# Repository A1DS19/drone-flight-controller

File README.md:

# Drone Flight Controller

A custom drone flight controller, designed in KiCad 10: an STM32F103R8T6 flight core paired with
an ATmega328P telemetry co-processor on a four-layer, ~102 × 49 mm PCB — taken from schematic
capture through placement, routing, clean ERC/DRC, and JLCPCB fabrication outputs
([pcb/production/](pcb/production/)).

## Features

- **STM32F103R8T6 flight core** — MPU-6050 IMU on I²C, four ESC/motor outputs, RC-receiver and
  TF-Luna LIDAR inputs, USB with ESD protection, SWD debug
- **ATmega328P telemetry co-processor** — nRF24L01P 2.4 GHz radio with SMA antenna connector,
  CH340G USB-serial, microSD logging over SPI, 5 V ↔ 3.3 V level shifting
- **Power tree** — XT60 battery input → LM7805 (5 V) → AMS1117 (3.3 V), filtered analog rail,
  battery-voltage sensing
- **0.96″ OLED** status display
- **Four-layer board** — solid internal ground plane, dedicated power planes, 71-line LCSC BOM,
  JLCPCB-ready Gerbers

## Screenshots

| Front | Back |
|-------|------|
|  |  |

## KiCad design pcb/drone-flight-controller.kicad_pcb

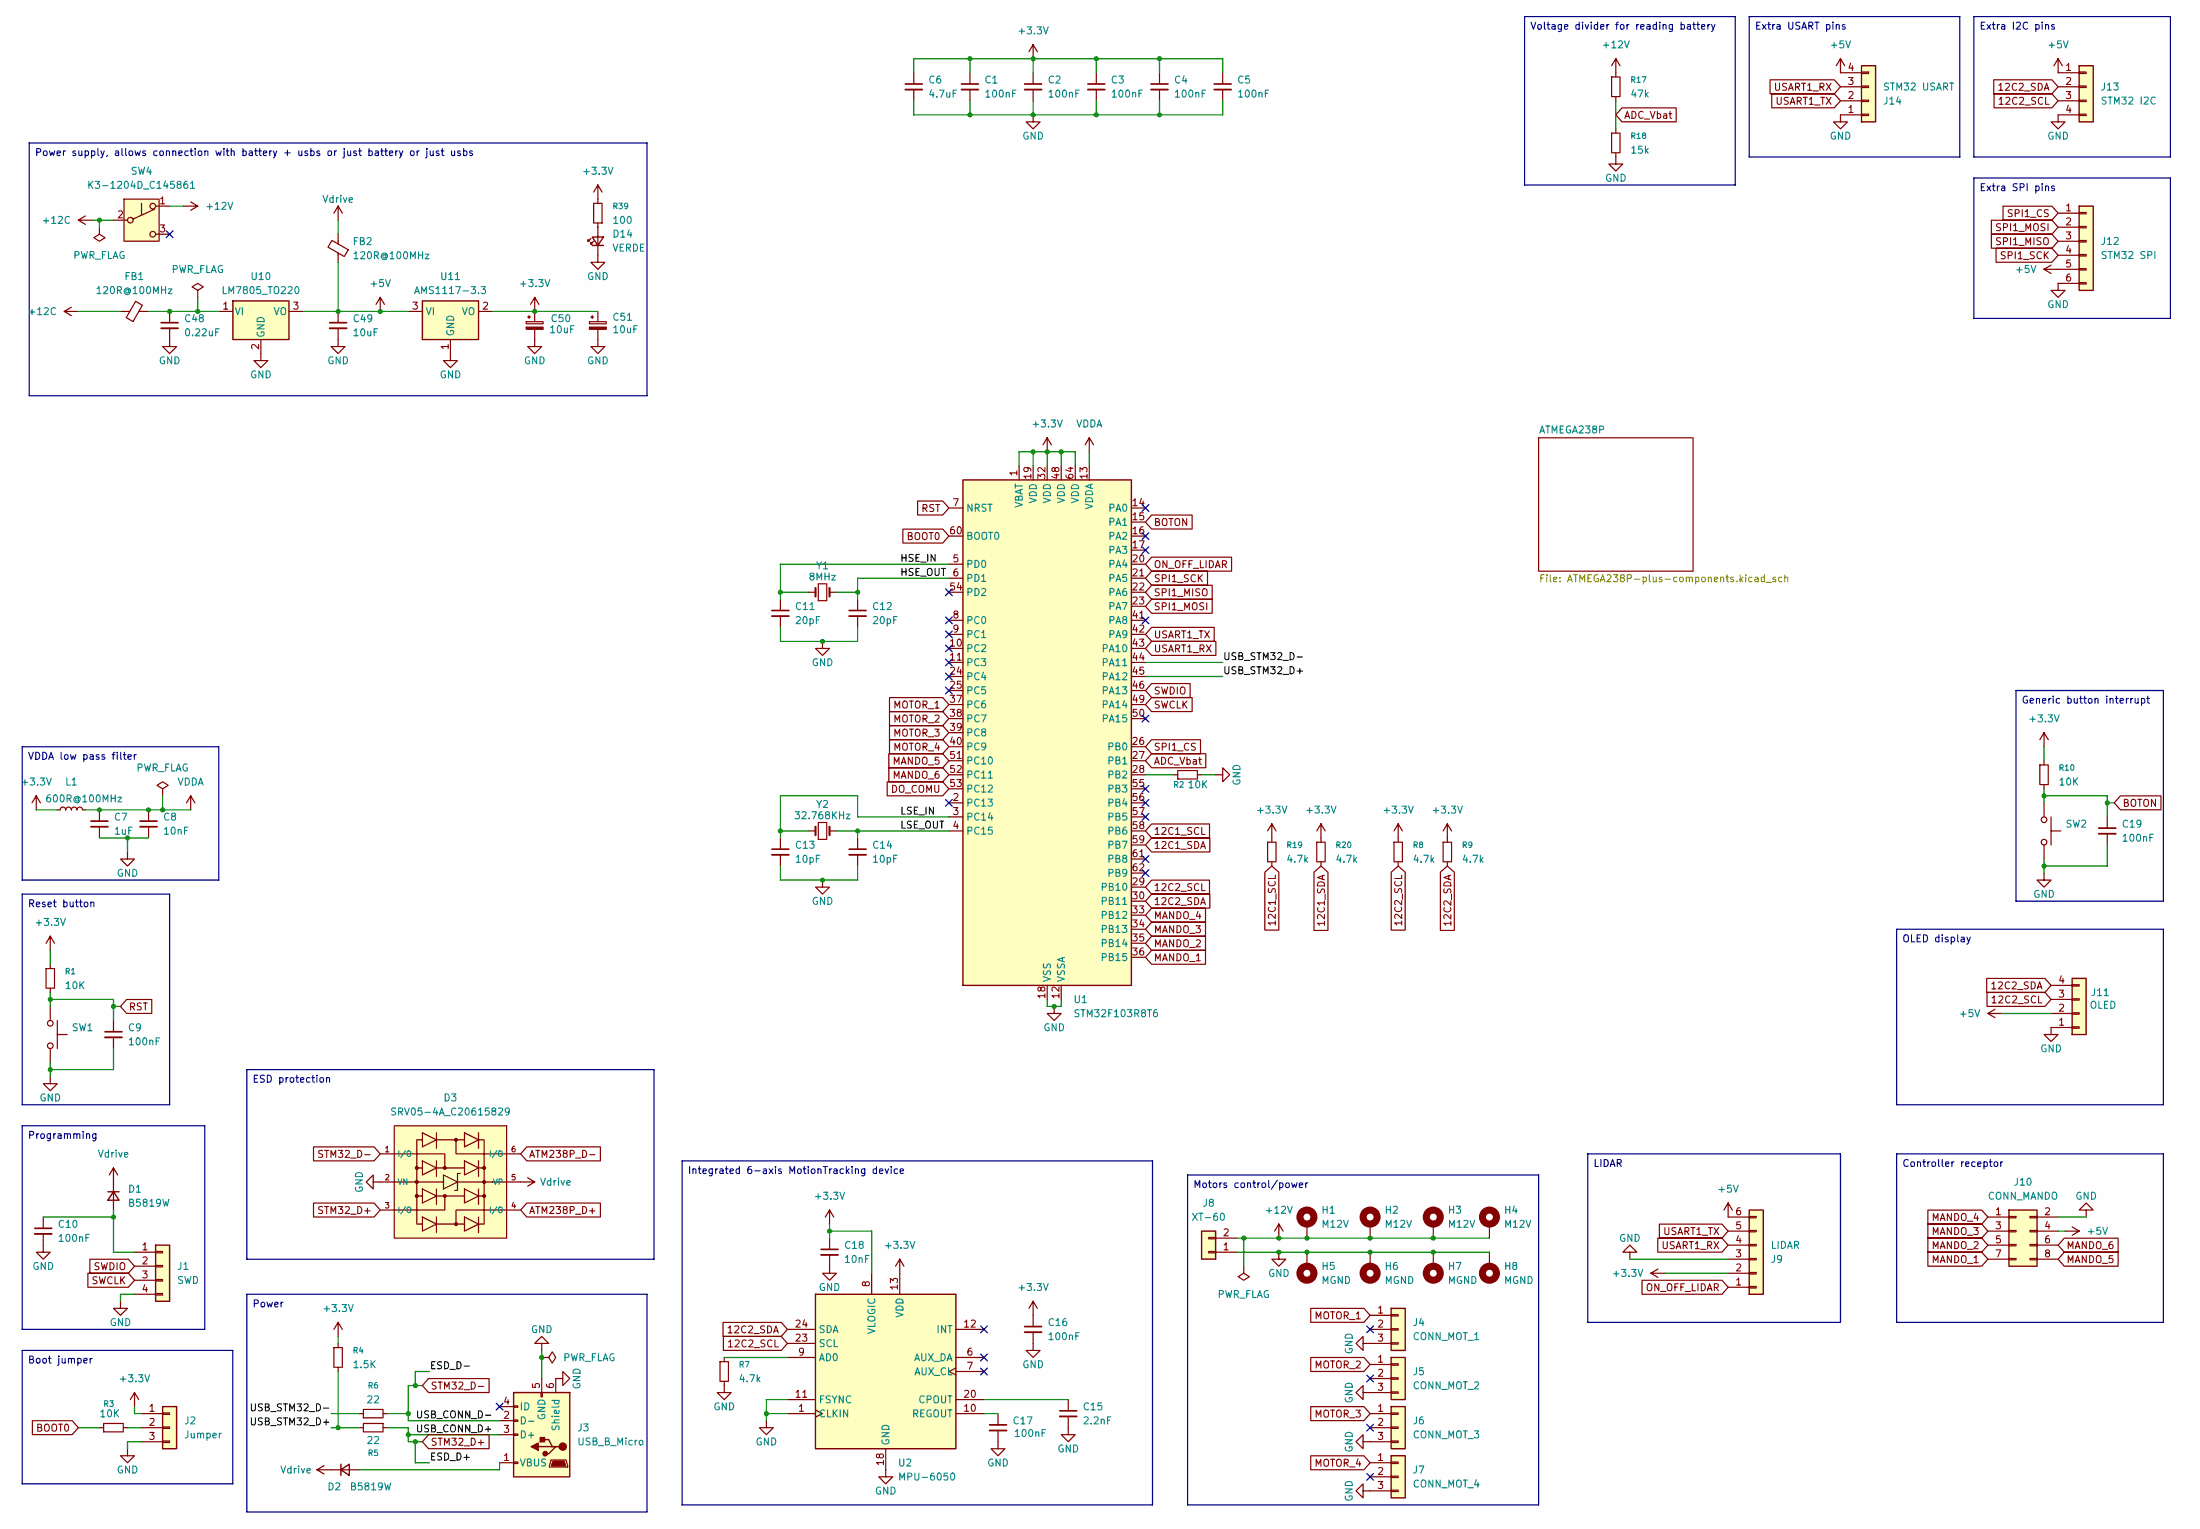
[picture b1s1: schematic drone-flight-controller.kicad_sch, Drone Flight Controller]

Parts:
C1, C2, C3, C4, C5, C9, C10, C16, C17, C19: 100nF; C_0402_1005Metric; Part CL05B104KO5NNNC; LCSC C1525
C6: 4.7uF; C_0402_1005Metric; Part CL05A475MQ5NRNC; LCSC C307423
C7: 1uF; C_0402_1005Metric; Part CL05A105KA5NQNC; LCSC C52923
C8, C18: 10nF; C_0402_1005Metric; Part CL05B103KB5NNNC; LCSC C15195
C11, C12: 20pF; C_0402_1005Metric; Part 0402CG200J500NT; LCSC C1554
C13, C14: 10pF; C_0402_1005Metric; Part CL05C100JB5NNNC; LCSC C32949
C15: 2.2nF; C_0402_1005Metric; Part 0402B222K500NT; LCSC C1531
C48: 0.22uF; C_1206_3216Metric; Part 1206B224K500NT; LCSC C1857
C49: 10uF; C_1206_3216Metric; Part CL31A106KBHNNNE; LCSC C13585
C50, C51: 10uF; C_1206_3216Metric; Part TAJA106K016RNJ; LCSC C7171
D1, D2: B5819W; D_SOD-123; Part B5819W; LCSC C64885
D3: SRV05-4A_C20615829; SOT-23-6_L2.9-W1.6-P0.95-LS2.9-BL; Part SRV05-4A; LCSC C20615829
D14: VERDE; LED_0603_1608Metric; Part KT-0603G; LCSC C12624
FB1, FB2: 120R@100MHz; L_0805_2012Metric; Part BLM21PG121SN1D; LCSC C79382
H1, H2, H3, H4: M12V; MountingHole_3.5mm_5.5mm
H5, H6, H7, H8: MGND; MountingHole_3.5mm_5.5mm
J1: SWD; PinHeader_1x04_P2.54mm_Vertical; Part PZ254V-11-04P; LCSC C2691448
J2: Jumper; PinHeader_1x03_P2.54mm_Vertical; Part PZ254V-11-03P; LCSC C2937625
J3: USB_B_Micro; MICRO-USB-SMD_MICROXNJ_1; Part MicroXNJ; LCSC C404969
J4: CONN_MOT_1; PinHeader_1x03_P2.54mm_Vertical; Part PZ254V-11-03P; LCSC C2937625
J5: CONN_MOT_2; PinHeader_1x03_P2.54mm_Vertical; Part PZ254V-11-03P; LCSC C2937625
J6: CONN_MOT_3; PinHeader_1x03_P2.54mm_Vertical; Part PZ254V-11-03P; LCSC C2937625
J7: CONN_MOT_4; PinHeader_1x03_P2.54mm_Vertical; Part PZ254V-11-03P; LCSC C2937625
J8: XT-60; AMASS_XT60-M; Part XT60-M.; LCSC C98733
J9: LIDAR; PinHeader_1x06_P2.54mm_Horizontal; Part PZ254V-11-06P; LCSC C492405
J10: CONN_MANDO; PinHeader_2x04_P2.54mm_Vertical; Part PZ254V-12-8P; LCSC C492421
J11: OLED; Part PZ254V-11-04P; LCSC C2691448
J12: STM32 SPI; PinHeader_1x06_P2.54mm_Vertical; Part PZ254V-11-06P; LCSC C492405
J13: STM32 I2C; PinHeader_1x04_P2.54mm_Vertical; Part PZ254V-11-04P; LCSC C2691448
J14: STM32 USART; PinHeader_1x04_P2.54mm_Horizontal; Part PZ254V-11-04P; LCSC C2691448
L1: 600R@100MHz; L_0402_1005Metric; Part BLM15AG601SN1D; LCSC C76884
R1, R2, R3, R10: 10K; R_0402_1005Metric; Part 0402WGF1002TCE; LCSC C25744
R4: 1.5K; R_0402_1005Metric; Part 0402WGF1501TCE; LCSC C25867
R5, R6: 22; R_0603_1608Metric; Part 0402WGF220JTCE; LCSC C25092
R7, R8, R9, R19, R20: 4.7k; R_0402_1005Metric; Part 0402WGF4701TCE; LCSC C25900
R17: 47k; R_0402_1005Metric; Part 0402WGF4702TCE; LCSC C25792
R18: 15k; R_0402_1005Metric; Part 0402WGF1502TCE; LCSC C25756
R39: 100; R_0603_1608Metric; Part 0402WGF1000TCE; LCSC C25076
SW1, SW2: TS-1088-AR02016_C720477; SW-SMD_L3.9-W3.0-P4.45; Part TS-1088-AR02016; LCSC C720477
SW4: K3-1204D_C145861; SW-TH_K3-1204D; Part K3-1204D; LCSC C145861
U1: STM32F103R8T6; LQFP-64_10x10mm_P0.5mm; Part STM32F103R8T6; LCSC C46034
U2: MPU-6050; InvenSense_QFN-24_4x4mm_P0.5mm; Part MPU-6050; LCSC C24112
U10: LM7805_TO220; TO-220-3_Horizontal_TabDown; Part L7805CV; LCSC C5189702
U11: AMS1117-3.3; SOT-223-3_TabPin2; Part AMS1117-3.3; LCSC C6186
Y1: 8MHz; Crystal_SMD_5032-2Pin_5.0x3.2mm; Part X50328MSB2GI; LCSC C115962
Y2: 32.768KHz; Crystal_SMD_3215-2Pin_3.2x1.5mm; Part Q13FC13500004; LCSC C32346

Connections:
12C1_SCL: R19.2, U1.58 (PB6); also elsewhere on the board
12C1_SDA: R20.2, U1.59 (PB7); also elsewhere on the board
12C2_SCL: J11.3, J13.3, R8.2, U1.29 (PB10), U2.23 (SCL)
12C2_SDA: J11.4, J13.2, R9.2, U1.30 (PB11), U2.24 (SDA)
+3.3V: C1.1, C2.1, C3.1, C4.1, C5.1, C6.1, C16.1, C18.1, C50.1, C51.1, J2.1, J9.2, L1.1, R1.1, R4.1, R8.1, R9.1, R10.1, R19.1, R20.1, R39.2, U1.1 (VBAT), U1.19 (VDD), U1.32 (VDD), U1.48 (VDD), U1.64 (VDD), U2.8 (VLOGIC), U2.13 (VDD), U11.2 (VO); also elsewhere on the board
+5V: C49.1, FB2.1, J9.6, J10.4, J11.2, J12.5, J13.1, J14.4, U10.3 (VO), U11.3 (VI); also elsewhere on the board
+12C: FB1.1, SW4.2 (B)
+12V: H1.1 (1_1), H2.1 (1_1), H3.1 (1_1), H4.1 (1_1), J8.2, R17.1, SW4.1 (A)
/HSE_IN: C11.1, U1.5 (PD0), Y1.1
/HSE_OUT: C12.1, U1.6 (PD1), Y1.2
/LSE_IN: C13.1, U1.3 (PC14), Y2.1
/LSE_OUT: C14.1, U1.4 (PC15), Y2.2
/USB_STM32_D+: R4.2, R5.2, U1.45 (PA12)
/USB_STM32_D-: R6.1, U1.44 (PA11)
ADC_Vbat: R17.2, R18.1, U1.27 (PB1)
ATM238P_D+: D3.4 (I/O); also elsewhere on the board
ATM238P_D-: D3.6 (I/O); also elsewhere on the board
BOOT0: R3.1, U1.60 (BOOT0)
BOTON: C19.1, R10.2, SW2.1, U1.15 (PA1); also elsewhere on the board
DO_COMU: U1.53 (PC12); also elsewhere on the board
GND: C1.2, C2.2, C3.2, C4.2, C5.2, C6.2, C7.2, C8.2, C9.2, C10.2, C11.2, C12.2, C13.2, C14.2, C15.2, C16.2, C17.2, C18.2, C19.2, C48.2, C49.2, C50.2, C51.2, D3.2 (VN), D14.1 (K), H5.1 (1_1), H6.1 (1_1), H7.1 (1_1), H8.1 (1_1), J1.4, J2.3, J3.5 (GND), J3.6 (Shield), J4.3, J5.3, J6.3, J7.3, J8.1, J9.3, J10.2, J11.1, J12.6, J13.4, J14.1, R2.2, R7.2, R18.2, SW1.2, SW2.2, U1.12 (VSSA), U1.18 (VSS), U1.31 (VSS), U1.47 (VSS), U1.63 (VSS), U2.1 (CLKIN), U2.11 (FSYNC), U2.18 (GND), U10.2 (GND), U11.1 (GND); also elsewhere on the board
MANDO_1: J10.7, U1.36 (PB15)
MANDO_2: J10.5, U1.35 (PB14)
MANDO_3: J10.3, U1.34 (PB13)
MANDO_4: J10.1, U1.33 (PB12)
MANDO_5: J10.8, U1.51 (PC10)
MANDO_6: J10.6, U1.52 (PC11)
MOTOR_1: J4.1, U1.37 (PC6)
MOTOR_2: J5.1, U1.38 (PC7)
MOTOR_3: J6.1, U1.39 (PC8)
MOTOR_4: J7.1, U1.40 (PC9)
unnamed: C10.1, D1.2 (A), J1.1
unnamed: D2.2 (A), J3.1 (VBUS)
unnamed: D14.2 (A), R39.1
unnamed: J2.2, R3.2
unnamed: R2.1, U1.28 (PB2)
unnamed: R7.1, U2.9 (AD0)
unnamed: C15.1, U2.20 (CPOUT)
unnamed: C17.1, U2.10 (REGOUT)
unnamed: C48.1, FB1.2, U10.1 (VI)
ON_OFF_LIDAR: J9.1, U1.20 (PA4)
RST: C9.1, R1.2, SW1.1, U1.7 (NRST); also elsewhere on the board
SPI1_CS: J12.1, U1.26 (PB0)
SPI1_MISO: J12.3, U1.22 (PA6)
SPI1_MOSI: J12.2, U1.23 (PA7)
SPI1_SCK: J12.4, U1.21 (PA5)
STM32_D+: D3.3 (I/O), J3.3 (D+), R5.1
STM32_D-: D3.1 (I/O), J3.2 (D-), R6.2
SWCLK: J1.3, U1.49 (PA14)
SWDIO: J1.2, U1.46 (PA13)
USART1_RX: J9.4, J14.3, U1.43 (PA10)
USART1_TX: J9.5, J14.2, U1.42 (PA9)
VDDA: C7.1, C8.1, L1.2, U1.13 (VDDA)
Vdrive: D1.1 (K), D2.1 (K), D3.5 (VP), FB2.2; also elsewhere on the board

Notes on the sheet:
Voltage divider for reading battery
Extra I2C pins
OLED display
Controller receptor
LIDAR
Motors control/power
Extra SPI pins
Power
Programming
Power supply, allows connection with battery + usbs or just battery or just usbs
Integrated 6-axis MotionTracking device
Extra USART pins
ESD protection
Boot jumper
VDDA low pass filter
Reset button
Generic button interrupt

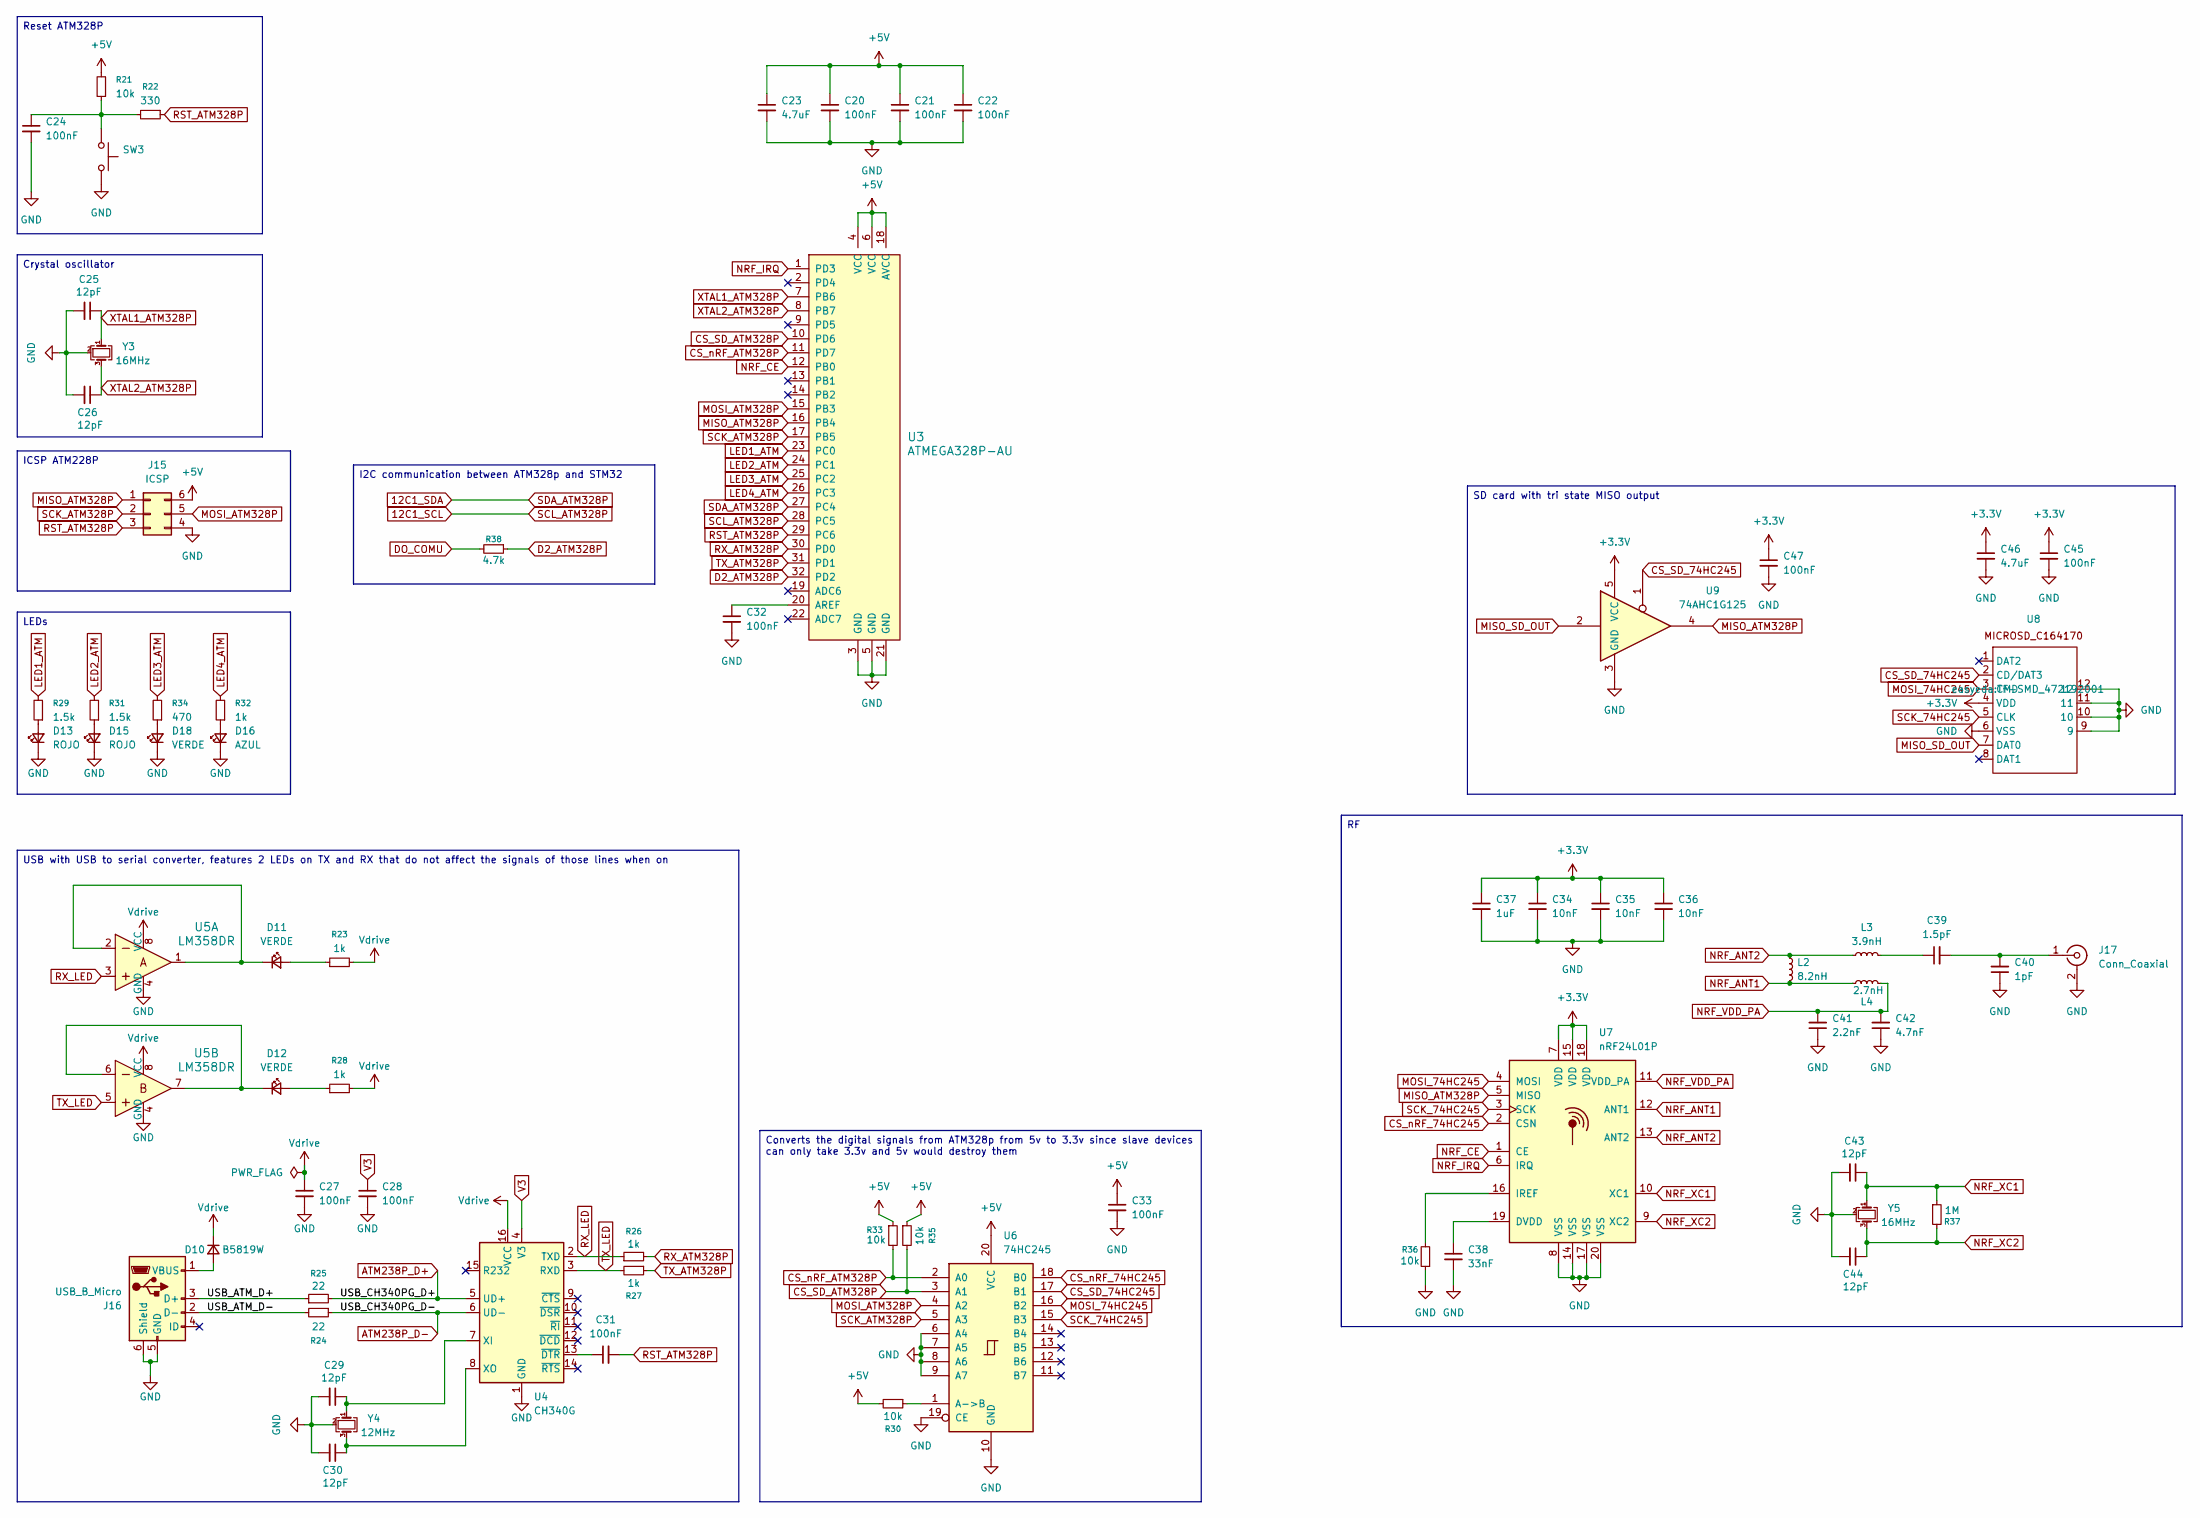
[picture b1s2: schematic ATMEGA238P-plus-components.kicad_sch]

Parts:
C20, C21, C22, C24, C27, C28, C31, C32, C33, C45, C47: 100nF; C_0402_1005Metric; Part CL05B104KO5NNNC; LCSC C1525
C23, C46: 4.7uF; C_0402_1005Metric; Part CL05A475MQ5NRNC; LCSC C307423
C25, C26, C29, C30, C43, C44: 12pF; C_0402_1005Metric; Part 0402CG120J500NT; LCSC C1547
C34, C35, C36: 10nF; C_0402_1005Metric; Part CL05B103KB5NNNC; LCSC C15195
C37: 1uF; C_0402_1005Metric; Part CL05A105KA5NQNC; LCSC C52923
C38: 33nF; C_0402_1005Metric; Part CC0402KRX7R9BB333; LCSC C106862
C39: 1.5pF; C_0402_1005Metric; Part 0402CG1R5C500NT; LCSC C1552
C40: 1pF; C_0402_1005Metric; Part 0402CG1R0C500NT; LCSC C1550
C41: 2.2nF; C_0402_1005Metric; Part 0402B222K500NT; LCSC C1531
C42: 4.7nF; C_0402_1005Metric; Part 0402B472K500NT; LCSC C1538
D10: B5819W; D_SOD-123; Part B5819W; LCSC C64885
D11, D12, D18: VERDE; LED_0603_1608Metric; Part KT-0603G; LCSC C12624
D13, D15: ROJO; LED_0603_1608Metric; Part KT-0603R; LCSC C2286
D16: AZUL; LED_0603_1608Metric; Part KT-0603B; LCSC C2288
J15: ICSP; PinHeader_2x03_P2.54mm_Vertical; Part PZ254V-12-6P; LCSC C492420
J16: USB_B_Micro; MICRO-USB-SMD_MICROXNJ_1; Part MicroXNJ; LCSC C404969
J17: Conn_Coaxial; SMA_142-0701-201; Part BWSMA-KWE-Z001; LCSC C496551
L2: 8.2nH; L_0402_1005Metric; Part LQG15HS8N2J02D; LCSC C98003
L3: 3.9nH; L_0402_1005Metric; Part SDCL1005C3N9STDF; LCSC C14033
L4: 2.7nH; L_0402_1005Metric; Part SDCL1005C2N7STDF; LCSC C27123
R21, R30, R33, R35, R36: 10k; R_0402_1005Metric; Part 0402WGF1002TCE; LCSC C25744
R22: 330; R_0402_1005Metric; Part 0402WGF3300TCE; LCSC C25104
R23, R28, R32: 1k; R_0603_1608Metric; Part 0603WAF1001T5E; LCSC C21190
R24, R25: 22; R_0603_1608Metric; Part 0402WGF220JTCE; LCSC C25092
R26, R27: 1k; R_0402_1005Metric; Part 0402WGF1001TCE; LCSC C11702
R29, R31: 1.5k; R_0603_1608Metric; Part 0603WAF1501T5E; LCSC C22843
R34: 470; R_0603_1608Metric; Part 0603WAF4700T5E; LCSC C23179
R37: 1M; R_0402_1005Metric; Part 0402WGF1004TCE; LCSC C26083
R38: 4.7k; R_0402_1005Metric; Part 0402WGF4701TCE; LCSC C25900
SW3: TS-1088-AR02016_C720477; SW-SMD_L3.9-W3.0-P4.45; Part TS-1088-AR02016; LCSC C720477
U3: ATMEGA328P-AU; TQFP-32_7x7mm_P0.8mm; MPN ATMEGA328P-AU; Digi-Key_PN ATMEGA328P-AU-ND
U4: CH340G; SOIC-16_3.9x9.9mm_P1.27mm; Part CH340G; LCSC C14267
U5: LM358DR; SOIC-8_3.9x4.9mm_P1.27mm; MPN LM358DR; Digi-Key_PN 296-1014-1-ND
U6: 74HC245; SOIC-20W_7.5x12.8mm_P1.27mm; Part SN74HC245DWR; LCSC C10093
U7: nRF24L01P; QFN-20-1EP_4x4mm_P0.5mm_EP2.5x2.5mm; Part NRF24L01P-R; LCSC C8791
U8: MICROSD_C164170; TF-SMD_472192001; Part 472192001; LCSC C164170
U9: 74AHC1G125; SOT-353_SC-70-5; Part SN74AHC1G125DCKR; LCSC C151890
Y3, Y5: 16MHz; Crystal_SMD_SeikoEpson_TSX3225-4Pin_3.2x2.5mm; Part X322516MLB4SI; LCSC C13738
Y4: 12MHz; Crystal_SMD_SeikoEpson_TSX3225-4Pin_3.2x2.5mm; Part X322512MSB4SI; LCSC C9002

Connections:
12C1_SCL: U3.28 (PC5); also elsewhere on the board
12C1_SDA: U3.27 (PC4); also elsewhere on the board
+3.3V: C34.1, C35.1, C36.1, C37.1, C45.1, C46.1, C47.1, U7.7 (VDD), U7.15 (VDD), U7.18 (VDD), U8.4 (VDD), U9.5 (VCC); also elsewhere on the board
+5V: C20.1, C21.1, C22.1, C23.1, C33.1, J15.6, R21.2, R30.2, R33.1, R35.1, U3.4 (VCC), U3.6 (VCC), U3.18 (AVCC), U6.20 (VCC); also elsewhere on the board
/ATMEGA238P/USB_ATM_D+: J16.3 (D+), R25.1
/ATMEGA238P/USB_ATM_D-: J16.2 (D-), R24.2
ATM238P_D+: R25.2, U4.5 (UD+); also elsewhere on the board
ATM238P_D-: R24.1, U4.6 (UD-); also elsewhere on the board
CS_SD_74HC245: U6.17 (B1), U8.2 (CD/DAT3), U9.1
CS_SD_ATM328P: R35.2, U3.10 (PD6), U6.3 (A1)
CS_nRF_74HC245: U6.18 (B0), U7.2 (CSN)
CS_nRF_ATM328P: R33.2, U3.11 (PD7), U6.2 (A0)
D2_ATM328P: R38.1, U3.32 (PD2)
DO_COMU: R38.2; also elsewhere on the board
GND: C20.2, C21.2, C22.2, C23.2, C24.2, C25.2, C26.2, C27.2, C28.2, C29.2, C30.2, C32.2, C33.2, C34.2, C35.2, C36.2, C37.2, C38.2, C40.1, C41.1, C42.1, C43.2, C44.2, C45.2, C46.2, C47.2, D13.1 (K), D15.1 (K), D16.1 (K), D18.1 (K), J15.4, J16.5 (GND), J16.6 (Shield), J17.2 (Ext), R36.1, SW3.2, U3.3 (GND), U3.5 (GND), U3.21 (GND), U4.1 (GND), U5.4 (GND), U6.6 (A4), U6.7 (A5), U6.8 (A6), U6.9 (A7), U6.10 (GND), U6.19 (CE), U7.8 (VSS), U7.14 (VSS), U7.17 (VSS), U7.20 (VSS), U8.6 (VSS), U8.9, U8.10, U8.11, U8.12, U9.3 (GND), Y3.2 (G), Y3.4 (G), Y4.2 (G), Y4.4 (G), Y5.2 (G), Y5.4 (G); also elsewhere on the board
LED1_ATM: R29.2, U3.23 (PC0)
LED2_ATM: R31.2, U3.24 (PC1)
LED3_ATM: R34.2, U3.25 (PC2)
LED4_ATM: R32.2, U3.26 (PC3)
MISO_ATM328P: J15.1, U3.16 (PB4), U7.5 (MISO), U9.4
MISO_SD_OUT: U8.7 (DAT0), U9.2
MOSI_74HC245: U6.16 (B2), U7.4 (MOSI), U8.3 (CMD)
MOSI_ATM328P: J15.5, U3.15 (PB3), U6.4 (A2)
NRF_ANT1: L2.2, L4.1, U7.12 (ANT1)
NRF_ANT2: L2.1, L3.1, U7.13 (ANT2)
NRF_CE: U3.12 (PB0), U7.1 (CE)
NRF_IRQ: U3.1 (PD3), U7.6 (IRQ)
NRF_VDD_PA: C41.2, C42.2, L4.2, U7.11 (VDD_PA)
NRF_XC1: C43.1, R37.1, U7.10 (XC1), Y5.1
NRF_XC2: C44.1, R37.2, U7.9 (XC2), Y5.3
unnamed 53: C24.1, R21.1, R22.2, SW3.1; also elsewhere on the board
unnamed: C39.1, L3.2
unnamed: D10.2 (A), J16.1 (VBUS)
unnamed: D11.2 (A), R23.1
unnamed: D11.1 (K), U5.1, U5.2
unnamed: D12.2 (A), R28.1
unnamed: D12.1 (K), U5.6, U5.7
unnamed: D13.2 (A), R29.1
unnamed: D15.2 (A), R31.1
unnamed: D16.2 (A), R32.1
unnamed: D18.2 (A), R34.1
unnamed: C39.2, C40.2, J17.1 (In)
unnamed: C32.1, U3.20 (AREF)
unnamed: C29.1, U4.7 (XI), Y4.1
unnamed: C30.1, U4.8 (XO), Y4.3
unnamed: C31.1, U4.13 (~DTR)
unnamed: R30.1, U6.1 (A->B)
unnamed: C38.1, U7.19 (DVDD)
unnamed: R36.2, U7.16 (IREF)
RST_ATM328P: C31.2, J15.3, R22.1, U3.29 (PC6)
RX_ATM328P: R26.2, U3.30 (PD0)
RX_LED: R26.1, U4.2 (TXD), U5.3
SCK_74HC245: U6.15 (B3), U7.3 (SCK), U8.5 (CLK)
SCK_ATM328P: J15.2, U3.17 (PB5), U6.5 (A3)
TX_ATM328P: R27.1, U3.31 (PD1)
TX_LED: R27.2, U4.3 (RXD), U5.5
V3: C28.1, U4.4 (V3)
Vdrive: C27.1, D10.1 (K), R23.2, R28.2, U4.16 (VCC), U5.8 (VCC); also elsewhere on the board
XTAL1_ATM328P: C25.1, U3.7 (PB6), Y3.1
XTAL2_ATM328P: C26.1, U3.8 (PB7), Y3.3

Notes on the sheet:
I2C communication between ATM328p and STM32
LEDs
SD card with tri state MISO output
USB with USB to serial converter, features 2 LEDs on TX and RX that do not affect the signals of those lines when on
Converts the digital signals from ATM328p from 5v to 3.3v since slave devices can only take 3.3v and 5v would destroy them
ICSP ATM228P
Crystal oscillator
Reset ATM328P

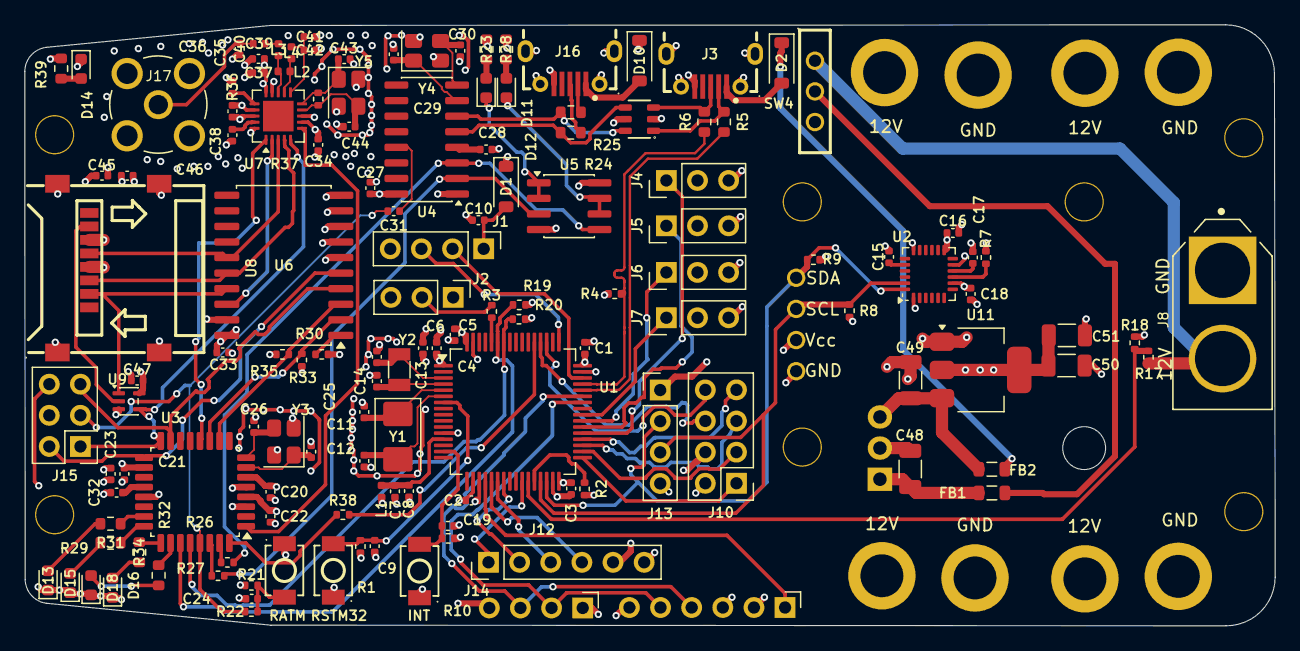
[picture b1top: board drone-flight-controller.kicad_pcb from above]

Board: 4 copper layers, 102.0 x 49.0 mm, 146 parts (1 on the bottom side), 105 nets.

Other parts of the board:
INT: TS-1088-AR02016_C720477; SW-SMD_L3.9-W3.0-P4.45
RATM: TS-1088-AR02016_C720477; SW-SMD_L3.9-W3.0-P4.45
RSTM32: TS-1088-AR02016_C720477; SW-SMD_L3.9-W3.0-P4.45

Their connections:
BOTON: INT.1; also elsewhere on the board
GND: INT.2, RATM.2, RSTM32.2; also elsewhere on the board
unnamed 53: RATM.1; also elsewhere on the board
RST: RSTM32.1; also elsewhere on the board

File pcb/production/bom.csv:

Designator,Footprint,Quantity,Value,LCSC Part #
"C1, C10, C16, C17, C19, C2, C20, C21, C22, C24, C27, C28, C3, C31, C32, C33, C4, C45, C47, C5, C9",0402,21,100nF,C1525
"C11, C12",0402,2,20pF,C1554
"C13, C14",0402,2,10pF,C32949
"C15, C41",0402,2,2.2nF,C1531
"C18, C34, C35, C36, C8",0402,5,10nF,C15195
"C23, C46, C6",0402,3,4.7uF,C307423
"C25, C26, C29, C30, C43, C44",0402,6,12pF,C1547
"C37, C7",0402,2,1uF,C52923
C38,0402,1,33nF,C106862
C39,0402,1,1.5pF,C1552
C40,0402,1,1pF,C1550
C42,0402,1,4.7nF,C1538
C48,1206,1,0.22uF,C1857
C49,1206,1,10uF,C13585
"C50, C51",1206,2,10uF,C7171
"D1, D10, D2",D_SOD-123,3,B5819W,C64885
"D11, D12, D14, D18",0603,4,VERDE,C12624
"D13, D15",0603,2,ROJO,C2286
D16,0603,1,AZUL,C2288
D3,SOT-23-6_L2.9-W1.6-P0.95-LS2.9-BL,1,SRV05-4A_C20615829,C20615829
"FB1, FB2",0805,2,120R@100MHz,C79382
"INT, RATM, RSTM32",SW-SMD_L3.9-W3.0-P4.45,3,TS-1088-AR02016_C720477,C720477
J1,PinHeader_1x04_P2.54mm_Vertical,1,SWD,C2691448
J10,PinHeader_2x04_P2.54mm_Vertical,1,CONN_MANDO,C492421
J11,OLED,1,OLED,C2691448
J12,PinHeader_1x06_P2.54mm_Vertical,1,STM32 SPI,C492405
J13,PinHeader_1x04_P2.54mm_Vertical,1,STM32 I2C,C2691448
J14,PinHeader_1x04_P2.54mm_Horizontal,1,STM32 USART,C2691448
J15,PinHeader_2x03_P2.54mm_Vertical,1,ICSP,C492420
"J16, J3",MICRO-USB-SMD_MICROXNJ_1,2,USB_B_Micro,C404969
J17,SMA_142-0701-201,1,Conn_Coaxial,C496551
J2,PinHeader_1x03_P2.54mm_Vertical,1,Jumper,C2937625
J4,PinHeader_1x03_P2.54mm_Vertical,1,CONN_MOT_1,C2937625
J5,PinHeader_1x03_P2.54mm_Vertical,1,CONN_MOT_2,C2937625
J6,PinHeader_1x03_P2.54mm_Vertical,1,CONN_MOT_3,C2937625
J7,PinHeader_1x03_P2.54mm_Vertical,1,CONN_MOT_4,C2937625
J8,AMASS_XT60-M,1,XT-60,C98733
J9,PinHeader_1x06_P2.54mm_Horizontal,1,LIDAR,C492405
L1,0402,1,600R@100MHz,C76884
L2,0402,1,8.2nH,C98003
L3,0402,1,3.9nH,C14033
L4,0402,1,2.7nH,C27123
"R1, R10, R2, R21, R3, R30, R33, R35, R36",0402,9,10K,C25744
R17,0402,1,47k,C25792
R18,0402,1,15k,C25756
"R19, R20, R38, R7, R8, R9",0402,6,4.7k,C25900
R22,0402,1,330,C25104
"R23, R28, R32",0603,3,1k,C21190
"R24, R25, R5, R6",0603,4,22,C25092
"R26, R27",0402,2,1k,C11702
"R29, R31",0603,2,1.5k,C22843
R34,0603,1,470,C23179
R37,0402,1,1M,C26083
R39,0603,1,100,C25076
R4,0402,1,1.5K,C25867
SW4,SW-TH_K3-1204D,1,K3-1204D_C145861,C145861
U1,LQFP-64_10x10mm_P0.5mm,1,STM32F103R8T6,C46034
U10,TO-220-3_Horizontal_TabDown,1,LM7805_TO220,C5189702
U11,SOT-223-3_TabPin2,1,AMS1117-3.3,C6186
U2,InvenSense_QFN-24_4x4mm_P0.5mm,1,MPU-6050,C24112
U3,TQFP-32_7x7mm_P0.8mm,1,ATMEGA328P-AU,C14877
U4,SOIC-16_3.9x9.9mm_P1.27mm,1,CH340G,C14267
U5,SOIC-8_3.9x4.9mm_P1.27mm,1,LM358DR,C5423
U6,SOIC-20W_7.5x12.8mm_P1.27mm,1,74HC245,C10093
U7,QFN-20-1EP_4x4mm_P0.5mm_EP2.5x2.5mm,1,nRF24L01P,C8791
U8,TF-SMD_472192001,1,MICROSD_C164170,C164170
U9,SOT-353_SC-70-5,1,74AHC1G125,C151890
Y1,Crystal_SMD_5032-2Pin_5.0x3.2mm,1,8MHz,C115962
Y2,Crystal_SMD_3215-2Pin_3.2x1.5mm,1,32.768KHz,C32346
"Y3, Y5",Crystal_SMD_SeikoEpson_TSX3225-4Pin_3.2x2.5mm,2,16MHz,C13738
Y4,Crystal_SMD_SeikoEpson_TSX3225-4Pin_3.2x2.5mm,1,12MHz,C9002
